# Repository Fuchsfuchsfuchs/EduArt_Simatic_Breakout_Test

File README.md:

# EduArt_Simatic_Breakout_Test

## Introduction

This repository contains the ECAD Files and the code for a project which was created in the time at my Internship at EduArt Robotics. On the top side of the Eduard Robot sits a breakout Board for the Simatic IoT 2050 GPIO Pins. The Board is connected to the IPC with a flat ribbon cable which could be prone to cracks. So a simple solution to test the Robot before shipping was searched for. You plug the Simatic_Breakout_Test in and run the IOT_PCB_TEST program on the Robot. LEDs indicate for each pin if the connection works.

## How to use

Flash the Arduino Nano with the **NANO_PCB_TEST.ino** and place the Testboard on the IoT Breakout on the back of the Eduard Robot. After that execute the **IOT_PCB_TEST.py** on the Robot.

First run 
```
chmod +x IOT_PCB_TEST.py
```
to make the file executable. After that you can run the programm with:
```
sudo python3 IOT_TEST_PCB.py
```

GPIOs D0 and D1 are not tested, they are non existent on the Breakout board and are used to communicate with the Motorcontrollers.
The GPIOs D2 - D7 are directly tested if they are connected. GPIOs D8 to D13 and A0 to A5 are tested in pairs. So A0 gets a Signal from the Arduino and D8 is set to Output a HIGH Signal, which the Arduino receives and the A0 and D8 LEDs will light up. If one of the GPIOs is not connected or doesnt work properly both LEDs (A0 and D8) will not work.
The paired GPIOs are the following: A0 and D8, A1 and D9, A2 and D10, A3 and D11, A4 and D12, A5 and D13.

## Bill of Materials (BOM)

| Component    | Datasheet | Amount | Value  |
| ------------ | --------- | ------ | ------ |
| LED 1        | [WS2812B](https://www.digikey.com/en/htmldatasheets/production/1829370/0/0/1/ws2812b)      | 18     |        |
| Capacitors   | ToDo      | 18     | 100 nF |
| Arduino Nano | [Arduino Nano](https://docs.arduino.cc/hardware/nano/)      | 1      |        |
| Resistor     | ToDo      | 1      | 10K    |
| LED 2        | ToDo      | 1      |        |

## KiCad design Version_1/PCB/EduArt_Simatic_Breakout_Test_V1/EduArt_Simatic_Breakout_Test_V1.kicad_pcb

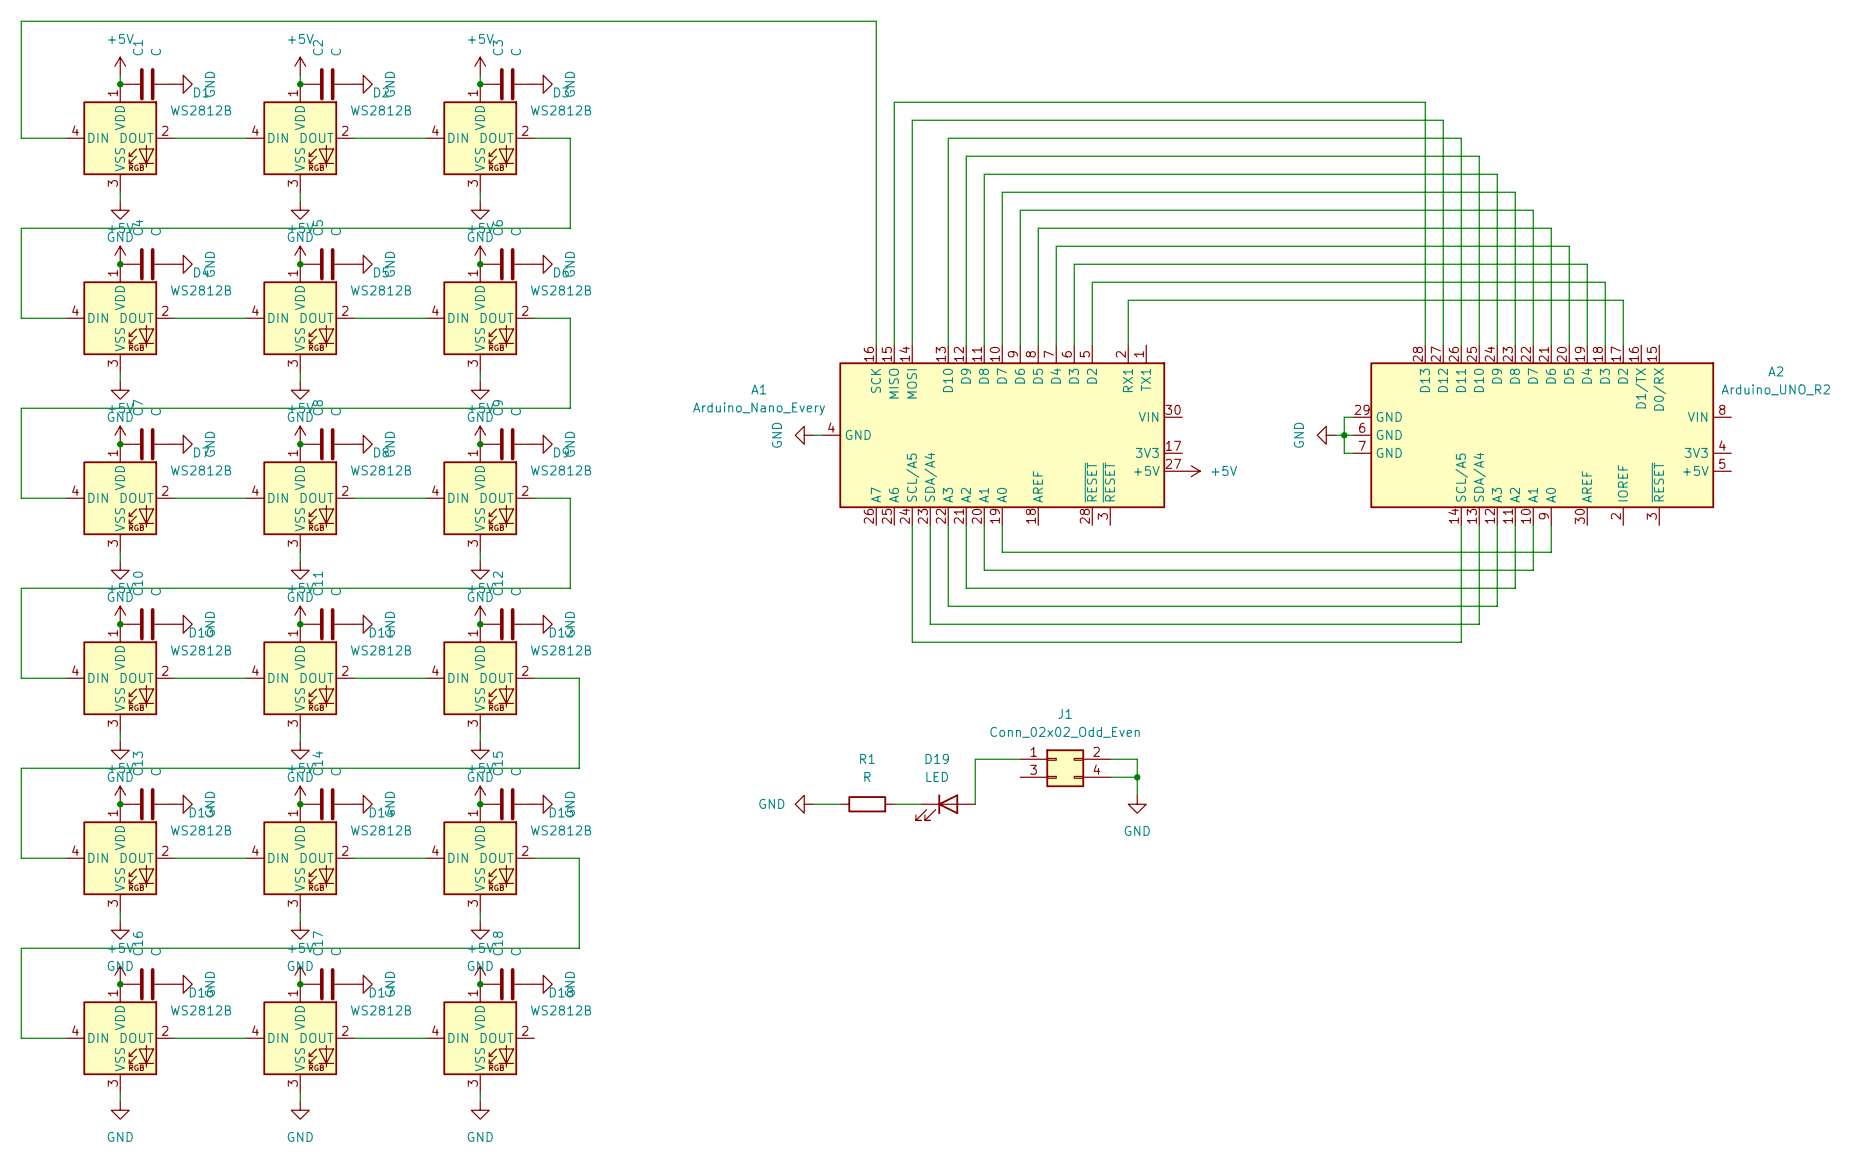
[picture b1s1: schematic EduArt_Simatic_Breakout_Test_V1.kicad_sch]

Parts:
A1: Arduino_Nano_Every; Arduino_Nano
A2: Arduino_UNO_R2
C1, C2, C3, C4, C5, C6, C7, C8, C9, C10, C11, C12, C13, C14, C15, C16, C17, C18: C; C_0603_1608Metric_Pad1.08x0.95mm_HandSolder
D1, D2, D3, D4, D5, D6, D7, D8, D9, D10, D11, D12, D13, D14, D15, D16, D17, D18: WS2812B; LED_WS2812B_PLCC4_5.0x5.0mm_P3.2mm
D19: LED; LED_0603_1608Metric_Pad1.05x0.95mm_HandSolder
J1: Conn_02x02_Odd_Even; PinHeader_2x02_P2.54mm_Vertical
R1: R; R_0603_1608Metric_Pad0.98x0.95mm_HandSolder

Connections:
+5V: A1.27 (+5V), C1.1, C2.1, C3.1, C4.1, C5.1, C6.1, C7.1, C8.1, C9.1, C10.1, C11.1, C12.1, C13.1, C14.1, C15.1, C16.1, C17.1, C18.1, D1.1 (VDD), D2.1 (VDD), D3.1 (VDD), D4.1 (VDD), D5.1 (VDD), D6.1 (VDD), D7.1 (VDD), D8.1 (VDD), D9.1 (VDD), D10.1 (VDD), D11.1 (VDD), D12.1 (VDD), D13.1 (VDD), D14.1 (VDD), D15.1 (VDD), D16.1 (VDD), D17.1 (VDD), D18.1 (VDD)
GND: A1.4 (GND), A1.29 (GND), A2.6 (GND), A2.7 (GND), A2.29 (GND), C1.2, C2.2, C3.2, C4.2, C5.2, C6.2, C7.2, C8.2, C9.2, C10.2, C11.2, C12.2, C13.2, C14.2, C15.2, C16.2, C17.2, C18.2, D1.3 (VSS), D2.3 (VSS), D3.3 (VSS), D4.3 (VSS), D5.3 (VSS), D6.3 (VSS), D7.3 (VSS), D8.3 (VSS), D9.3 (VSS), D10.3 (VSS), D11.3 (VSS), D12.3 (VSS), D13.3 (VSS), D14.3 (VSS), D15.3 (VSS), D16.3 (VSS), D17.3 (VSS), D18.3 (VSS), J1.2, J1.4, R1.1
unnamed: A1.19 (A0), A2.9 (A0)
unnamed: A1.20 (A1), A2.10 (A1)
unnamed: A1.21 (A2), A2.11 (A2)
unnamed: A1.22 (A3), A2.12 (A3)
unnamed: A1.5 (D2), A2.18 (D3)
unnamed: A1.6 (D3), A2.19 (D4)
unnamed: A1.7 (D4), A2.20 (D5)
unnamed: A1.8 (D5), A2.21 (D6)
unnamed: A1.9 (D6), A2.22 (D7)
unnamed: A1.10 (D7), A2.23 (D8)
unnamed: A1.11 (D8), A2.24 (D9)
unnamed: A1.12 (D9), A2.25 (D10)
unnamed: A1.13 (D10), A2.26 (D11)
unnamed: A1.15 (MISO), A2.28 (D13)
unnamed: A1.14 (MOSI), A2.27 (D12)
unnamed: A1.2 (RX1), A2.17 (D2)
unnamed: A1.16 (SCK), D1.4 (DIN)
unnamed: A1.24 (SCL/A5), A2.14 (SCL/A5)
unnamed: A1.23 (SDA/A4), A2.13 (SDA/A4)
unnamed: D1.2 (DOUT), D2.4 (DIN)
unnamed: D2.2 (DOUT), D3.4 (DIN)
unnamed: D3.2 (DOUT), D4.4 (DIN)
unnamed: D4.2 (DOUT), D5.4 (DIN)
unnamed: D5.2 (DOUT), D6.4 (DIN)
unnamed: D6.2 (DOUT), D7.4 (DIN)
unnamed: D7.2 (DOUT), D8.4 (DIN)
unnamed: D8.2 (DOUT), D9.4 (DIN)
unnamed: D9.2 (DOUT), D10.4 (DIN)
unnamed: D10.2 (DOUT), D11.4 (DIN)
unnamed: D11.2 (DOUT), D12.4 (DIN)
unnamed: D12.2 (DOUT), D13.4 (DIN)
unnamed: D13.2 (DOUT), D14.4 (DIN)
unnamed: D14.2 (DOUT), D15.4 (DIN)
unnamed: D15.2 (DOUT), D16.4 (DIN)
unnamed: D16.2 (DOUT), D17.4 (DIN)
unnamed: D17.2 (DOUT), D18.4 (DIN)
unnamed: D19.2 (A), J1.1
unnamed: D19.1 (K), R1.2

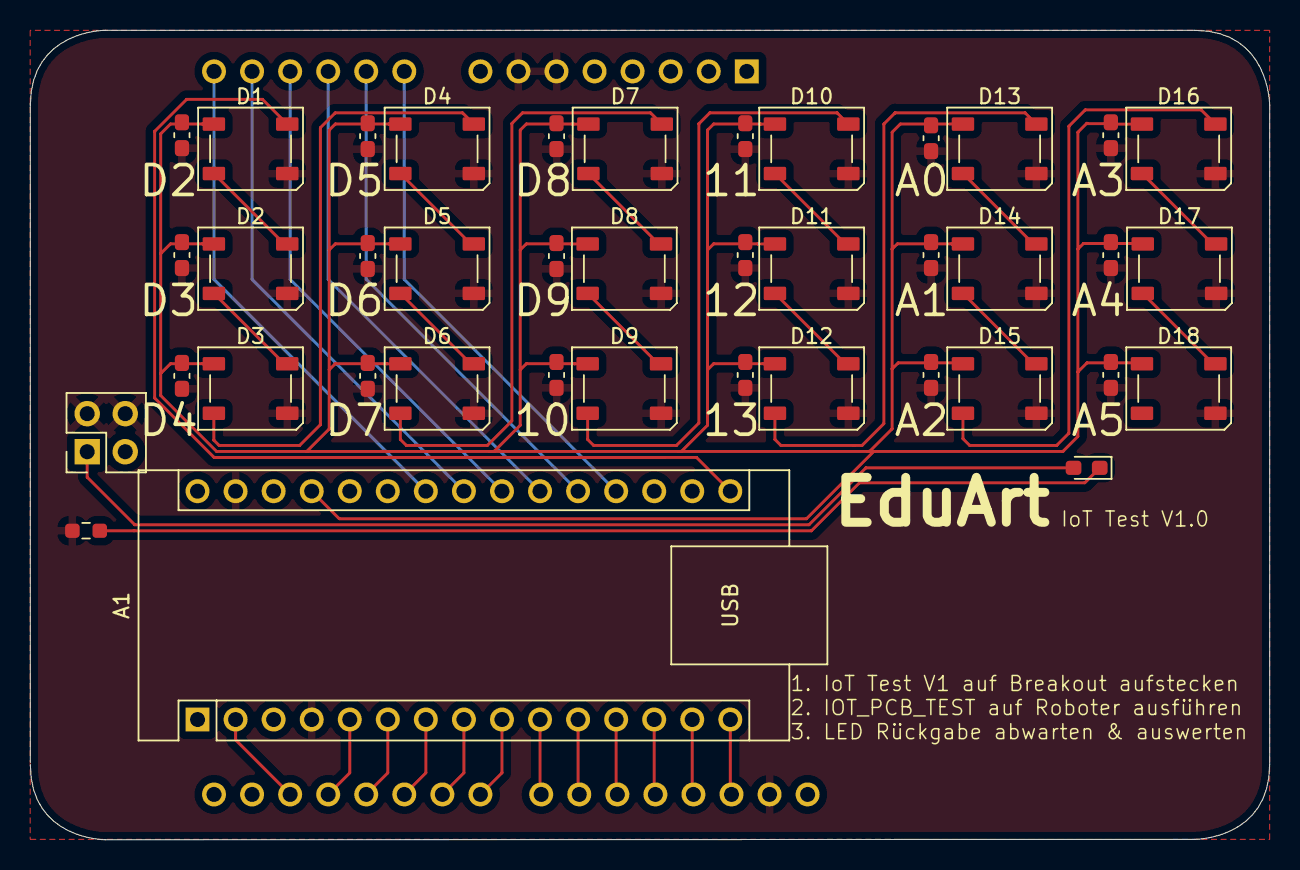
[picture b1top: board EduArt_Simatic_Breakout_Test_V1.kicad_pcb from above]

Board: 2 copper layers, 82.7 x 54.0 mm, 41 parts (1 on the bottom side), 40 nets.

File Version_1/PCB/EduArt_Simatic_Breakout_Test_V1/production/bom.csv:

Designator,Footprint,Quantity,Value,LCSC Part #
A1,Arduino_Nano,1,Arduino_Nano_Every,
A2,Arduino_UNO_R2,1,Arduino_UNO_R2,
"C1, C10, C11, C12, C13, C14, C15, C16, C17, C18, C2, C3, C4, C5, C6, C7, C8, C9",0603,18,C,
"D1, D10, D11, D12, D13, D14, D15, D16, D17, D18, D2, D3, D4, D5, D6, D7, D8, D9",LED_WS2812B_PLCC4_5.0x5.0mm_P3.2mm,18,WS2812B,
D19,0603,1,LED,
J1,PinHeader_2x02_P2.54mm_Vertical,1,Conn_02x02_Odd_Even,
R1,0603,1,R,
